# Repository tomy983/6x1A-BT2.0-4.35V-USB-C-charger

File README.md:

# 6x1A-BT2.0-4.35V-USB-C-charger
6 1S lipo cells charger with BT2.0 connectors - 1A charge current (each) - USB-C PD powered

Untested project.

The way it should work is:

12V via USB-C PD is requested. If the supply will comply 12V Vbus goes trough an 8A buck conveter to deliver 5V to each of 6 individual 4.35V 1A charger IC.

A green LED indicates 12V rail from PD present.

Green and red leds near each BT2.0 connector indicates charging status.

The BOM is made with JLCPCB component list in mind. Current production quote is 39€ for 2 pcs.

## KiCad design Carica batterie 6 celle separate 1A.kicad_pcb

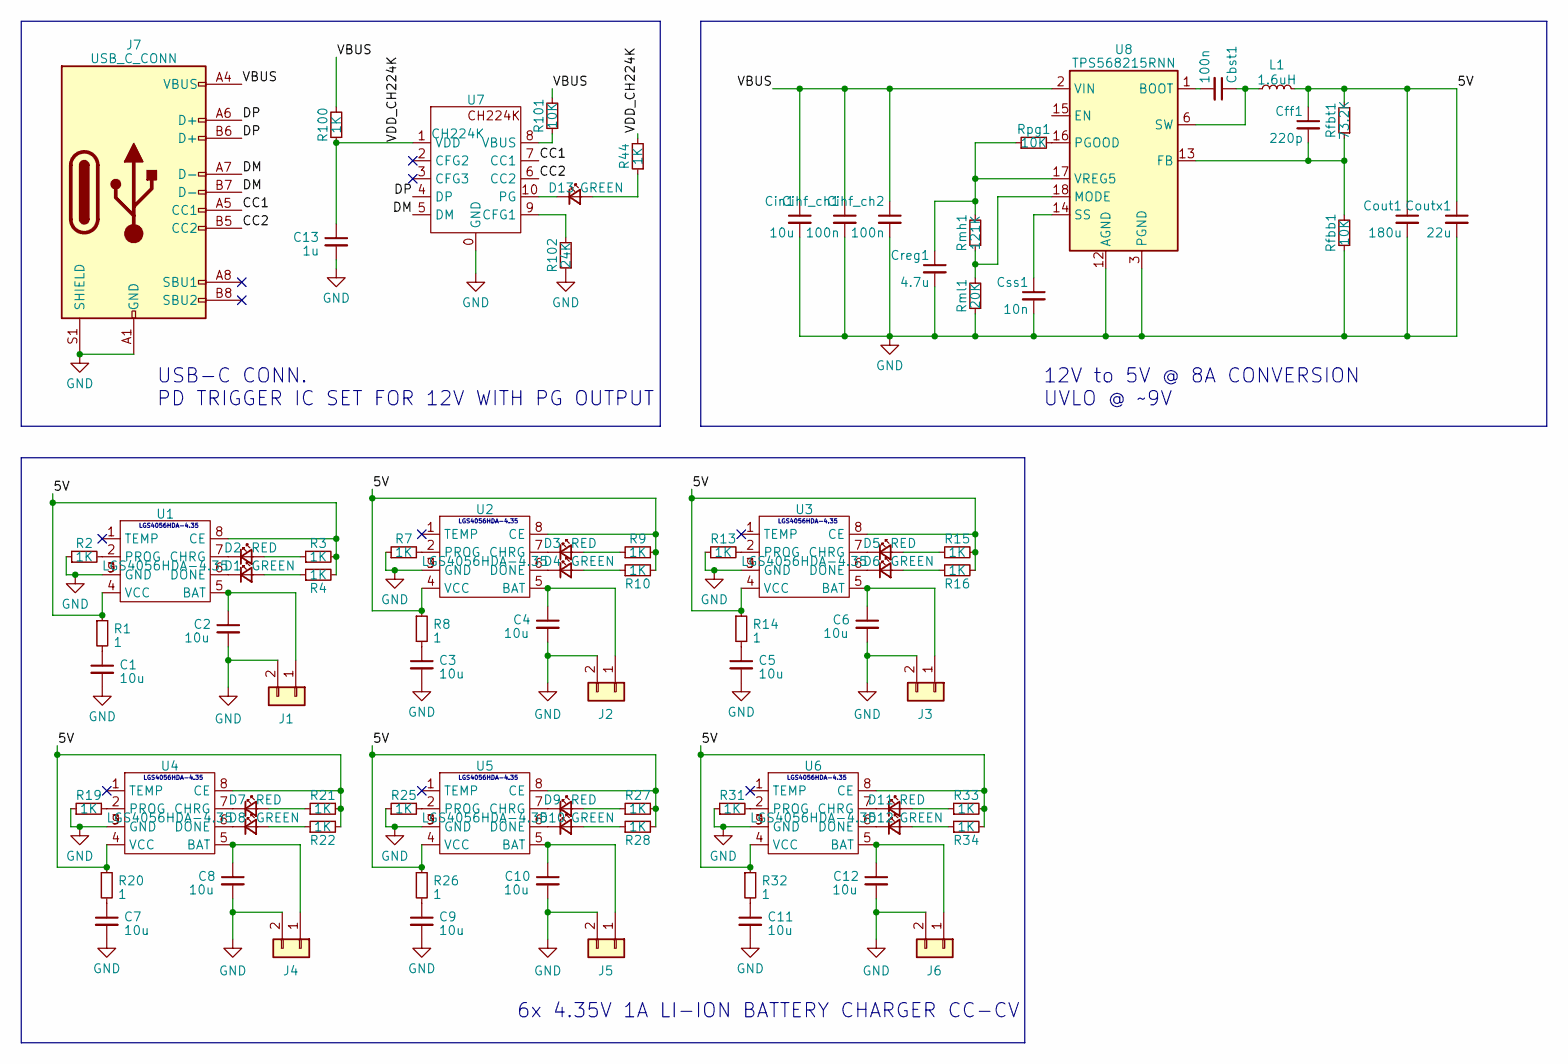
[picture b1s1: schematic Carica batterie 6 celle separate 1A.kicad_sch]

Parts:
C1, C2, C3, C4, C5, C6, C7, C8, C9, C10, C11, C12: 10u; C_0603_1608Metric
C13: 1u; C_0603_1608Metric; MPN CL10A105KB8NNNC
Cbst1: 100n; C_1206_3216Metric; MPN GRM31C5C1H104JA01K
Cff1: 220p; C_0402_1005Metric; MPN GRM1555C1H221JA01J
Cihf_ch1, Cihf_ch2: 100n; C_0603_1608Metric; MPN GRM188R71H104KA93D
Cin1: 10u; C_1210_3225Metric; MPN GRM32ER71J106KA12L
Cout1: 180u; CP_Elec_6.3x5.9; MPN 16SVPF180M
Coutx1: 22u; C_0805_2012Metric; MPN GRM21BR61A226ME44L
Creg1: 4.7u; C_0603_1608Metric; MPN CC0603KRX7R9BB822
Css1: 10n; C_0603_1608Metric; MPN CC0603KRX7R9BB822
D1, D4, D6, D8, D10, D12, D13: GREEN; LED_0603_1608Metric; MPN 19-217/GHC-YR1S2/3T
D2, D3, D5, D7, D9, D11: RED; LED_0603_1608Metric; MPN 19-213/R6W-BP2Q2B/3T
J1, J2, J3, J4, J5, J6: Conn_01x02; BT2.0; MPN betafpv BT2.0 MALE
J7: USB_C_CONN; USB_C_Receptacle_G-Switch_GT-USB-7010ASV; MPN GT-USB-7010ASV
L1: 1.6uH; L_Chilisin_BMRF00101040; MPN YSPI1040-1R5M
R1, R8, R14, R20, R26, R32: 1; R_0603_1608Metric
R2, R3, R4, R7, R9, R10, R13, R15, R16, R19, R21, R22, R25, R27, R28, R31, R33, R34, R44, R100: 1K; R_0603_1608Metric
R101: 10K; R_0603_1608Metric
R102: 24K; R_0603_1608Metric
Rfbb1: 10K; R_0603_1608Metric
Rfbt1: 73.2K; R_0603_1608Metric
Rmh1: 121K; R_0603_1608Metric
Rml1: 20K; R_0603_1608Metric
Rpg1: 10K; R_0603_1608Metric
U1, U2, U3, U4, U5, U6: LGS4056HDA-4.35; DFN-8-1EP_2x2mm_P0.5mm_EP0.9x1.6mm; MPN LGS4056HDA-4.35
U7: CH224K; ESSOP10; MPN CH224K
U8: TPS568215RNN; Texas_RNN0018A; MPN TPS568215RNN

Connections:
/5V: Cff1.1, Cout1.1, Coutx1.1, L1.2, R1.1, R3.2, R4.2, R8.1, R9.2, R10.2, R14.1, R15.2, R16.2, R20.1, R21.2, R22.2, R26.1, R27.2, R28.2, R32.1, R33.2, R34.2, Rfbt1.2, U1.4 (VCC), U1.8 (CE), U2.4 (VCC), U2.8 (CE), U3.4 (VCC), U3.8 (CE), U4.4 (VCC), U4.8 (CE), U5.4 (VCC), U5.8 (CE), U6.4 (VCC), U6.8 (CE)
/CC1: J7.A5 (CC1), U7.7 (CC1)
/CC2: J7.B5 (CC2), U7.6 (CC2)
/DM: J7.A7 (D-), J7.B7 (D-), U7.5 (DM)
/DP: J7.A6 (D+), J7.B6 (D+), U7.4 (DP)
/VBUS: Cihf_ch1.1, Cihf_ch2.1, Cin1.1, J7.A4 (VBUS), J7.A9 (VBUS), J7.B4 (VBUS), J7.B9 (VBUS), R100.2, R101.2, U8.2 (VIN), U8.11 (VIN)
/VDD_CH224K: C13.1, R44.2, R100.1, U7.1 (VDD)
GND: C1.2, C2.2, C3.2, C4.2, C5.2, C6.2, C7.2, C8.2, C9.2, C10.2, C11.2, C12.2, C13.2, Cihf_ch1.2, Cihf_ch2.2, Cin1.2, Cout1.2, Coutx1.2, Creg1.2, Css1.2, J1.2, J2.2, J3.2, J4.2, J5.2, J6.2, J7.A1 (GND), J7.A12 (GND), J7.B1 (GND), J7.B12 (GND), J7.S1 (SHIELD), R2.1, R7.1, R13.1, R19.1, R25.1, R31.1, R102.1, Rfbb1.1, Rml1.1, U1.3 (GND), U1.9 (GND), U2.3 (GND), U2.9 (GND), U3.3 (GND), U3.9 (GND), U4.3 (GND), U4.9 (GND), U5.3 (GND), U5.9 (GND), U6.3 (GND), U6.9 (GND), U7.0 (GND), U8.3 (PGND), U8.4 (PGND), U8.5 (PGND), U8.8 (PGND), U8.9 (PGND), U8.10 (PGND), U8.12 (AGND)
unnamed: C1.1, R1.2
unnamed: C3.1, R8.2
unnamed: C5.1, R14.2
unnamed: C7.1, R20.2
unnamed: C9.1, R26.2
unnamed: C11.1, R32.2
unnamed: Cbst1.1, L1.1, U8.6 (SW), U8.7 (SW)
unnamed: D1.2 (A), R4.1
unnamed: D1.1 (K), U1.6 (DONE)
unnamed: D2.2 (A), R3.1
unnamed: D2.1 (K), U1.7 (CHRG)
unnamed: D3.2 (A), R9.1
unnamed: D3.1 (K), U2.7 (CHRG)
unnamed: D4.2 (A), R10.1
unnamed: D4.1 (K), U2.6 (DONE)
unnamed: D5.2 (A), R15.1
unnamed: D5.1 (K), U3.7 (CHRG)
unnamed: D6.2 (A), R16.1
unnamed: D6.1 (K), U3.6 (DONE)
unnamed: D7.2 (A), R21.1
unnamed: D7.1 (K), U4.7 (CHRG)
unnamed: D8.2 (A), R22.1
unnamed: D8.1 (K), U4.6 (DONE)
unnamed: D9.2 (A), R27.1
unnamed: D9.1 (K), U5.7 (CHRG)
unnamed: D10.2 (A), R28.1
unnamed: D10.1 (K), U5.6 (DONE)
unnamed: D11.2 (A), R33.1
unnamed: D11.1 (K), U6.7 (CHRG)
unnamed: D12.2 (A), R34.1
unnamed: D12.1 (K), U6.6 (DONE)
unnamed: D13.2 (A), R44.1
unnamed: D13.1 (K), U7.10 (PG)
unnamed: C2.1, J1.1, U1.5 (BAT)
unnamed: C4.1, J2.1, U2.5 (BAT)
unnamed: C6.1, J3.1, U3.5 (BAT)
unnamed: C8.1, J4.1, U4.5 (BAT)
unnamed: C10.1, J5.1, U5.5 (BAT)
unnamed: C12.1, J6.1, U6.5 (BAT)
unnamed: R2.2, U1.2 (PROG)
unnamed: R7.2, U2.2 (PROG)
unnamed: R13.2, U3.2 (PROG)
unnamed: R19.2, U4.2 (PROG)
unnamed: R25.2, U5.2 (PROG)
unnamed: R31.2, U6.2 (PROG)
unnamed: R102.2, U7.9 (CFG1)
unnamed: R101.1, U7.8 (VBUS)
unnamed: Cbst1.2, U8.1 (BOOT)
unnamed: Cff1.2, Rfbb1.2, Rfbt1.1, U8.13 (FB)
unnamed: Rmh1.1, Rml1.2, U8.18 (MODE)
unnamed: Rpg1.2, U8.16 (PGOOD)
unnamed: Css1.1, U8.14 (SS)
unnamed: Creg1.1, Rmh1.2, Rpg1.1, U8.17 (VREG5)

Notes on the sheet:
LGS4056HDA-4.35
6x 4.35V 1A LI-ION BATTERY CHARGER CC-CV
USB-C CONN. PD TRIGGER IC SET FOR 12V WITH PG OUTPUT
12V to 5V @ 8A CONVERSION UVLO @ ~9V

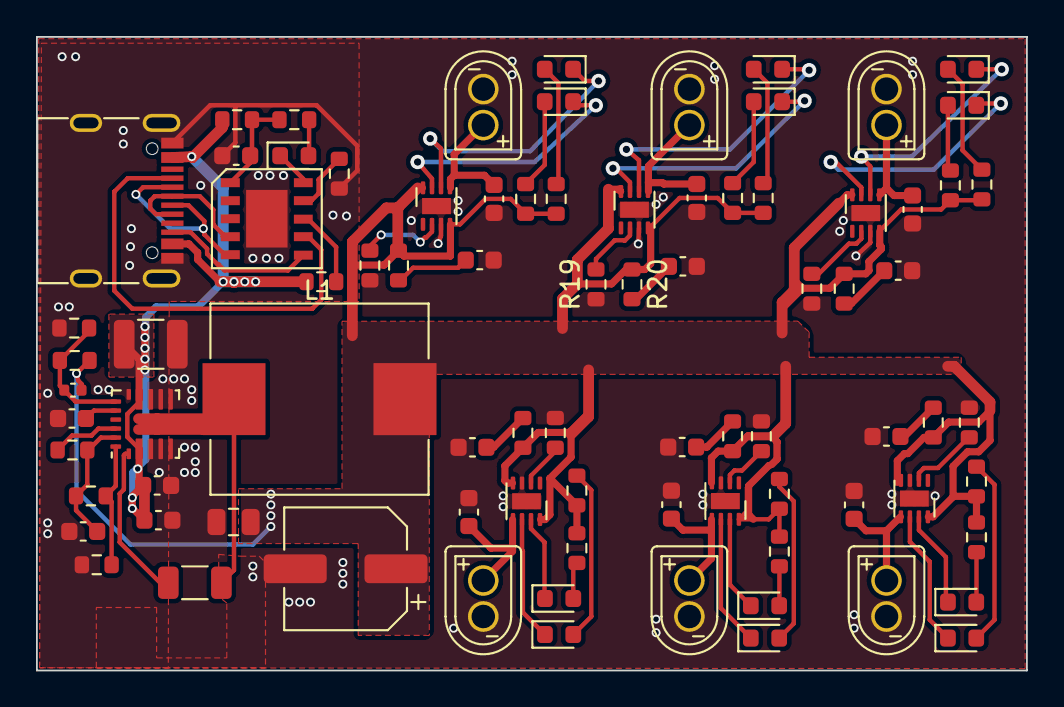
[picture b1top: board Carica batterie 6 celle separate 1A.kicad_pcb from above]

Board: 2 copper layers, 55.0 x 35.2 mm, 84 parts (0 on the bottom side), 61 nets.

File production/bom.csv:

Designator,Footprint,Quantity,Value,LCSC Part #
"C1, C10, C11, C12, C2, C3, C4, C5, C6, C7, C8, C9",0603,12,10u,
C13,0603,1,1u,CL10A105KB8NNNC
Cbst1,1206,1,100n,GRM31C5C1H104JA01K
Cff1,0402,1,220p,GRM1555C1H221JA01J
"Cihf_ch1, Cihf_ch2",0603,2,100n,GRM188R71H104KA93D
Cin1,1210,1,10u,GRM32ER71J106KA12L
Cout1,CP_Elec_6.3x5.9,1,180u,16SVPF180M
Coutx1,0805,1,22u,GRM21BR61A226ME44L
Creg1,0603,1,4.7u,CC0603KRX7R9BB822
Css1,0603,1,10n,CC0603KRX7R9BB822
"D1, D10, D12, D13, D4, D6, D8",0603,7,GREEN,19-217/GHC-YR1S2/3T
"D11, D2, D3, D5, D7, D9",0603,6,RED,19-213/R6W-BP2Q2B/3T
"J1, J2, J3, J4, J5, J6",BT2.0,6,Conn_01x02,betafpv BT2.0 MALE
J7,USB_C_Receptacle_G-Switch_GT-USB-7010ASV,1,USB_C_CONN,GT-USB-7010ASV
L1,L_Chilisin_BMRF00101040,1,1.6uH,YSPI1040-1R5M
"R1, R14, R20, R26, R32, R8",0603,6,1,
"R10, R100, R13, R15, R16, R19, R2, R21, R22, R25, R27, R28, R3, R31, R33, R34, R4, R44, R7, R9",0603,20,1K,
"R101, Rfbb1, Rpg1",0603,3,10K,
R102,0603,1,24K,
Rfbt1,0603,1,73.2K,
Rmh1,0603,1,121K,
Rml1,0603,1,20K,
"U1, U2, U3, U4, U5, U6",DFN-8-1EP_2x2mm_P0.5mm_EP0.9x1.6mm,6,LGS4056HDA-4.35,LGS4056HDA-4.35
U7,ESSOP10,1,CH224K,CH224K
U8,Texas_RNN0018A,1,TPS568215RNN,TPS568215RNN
